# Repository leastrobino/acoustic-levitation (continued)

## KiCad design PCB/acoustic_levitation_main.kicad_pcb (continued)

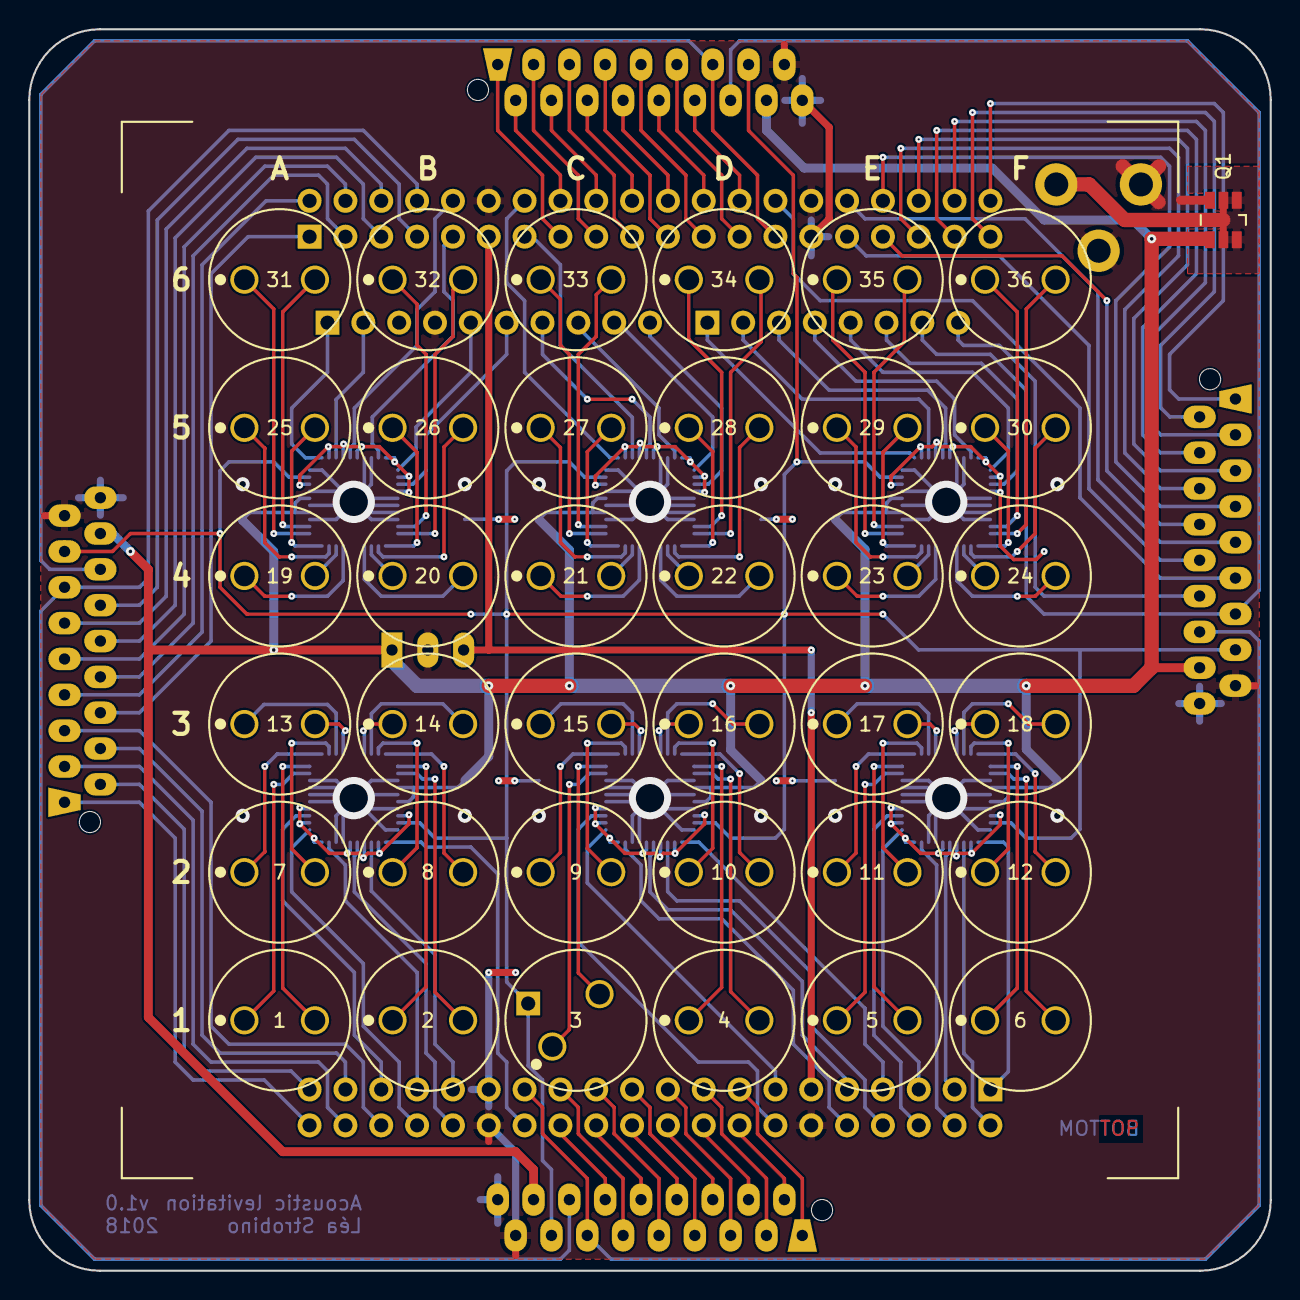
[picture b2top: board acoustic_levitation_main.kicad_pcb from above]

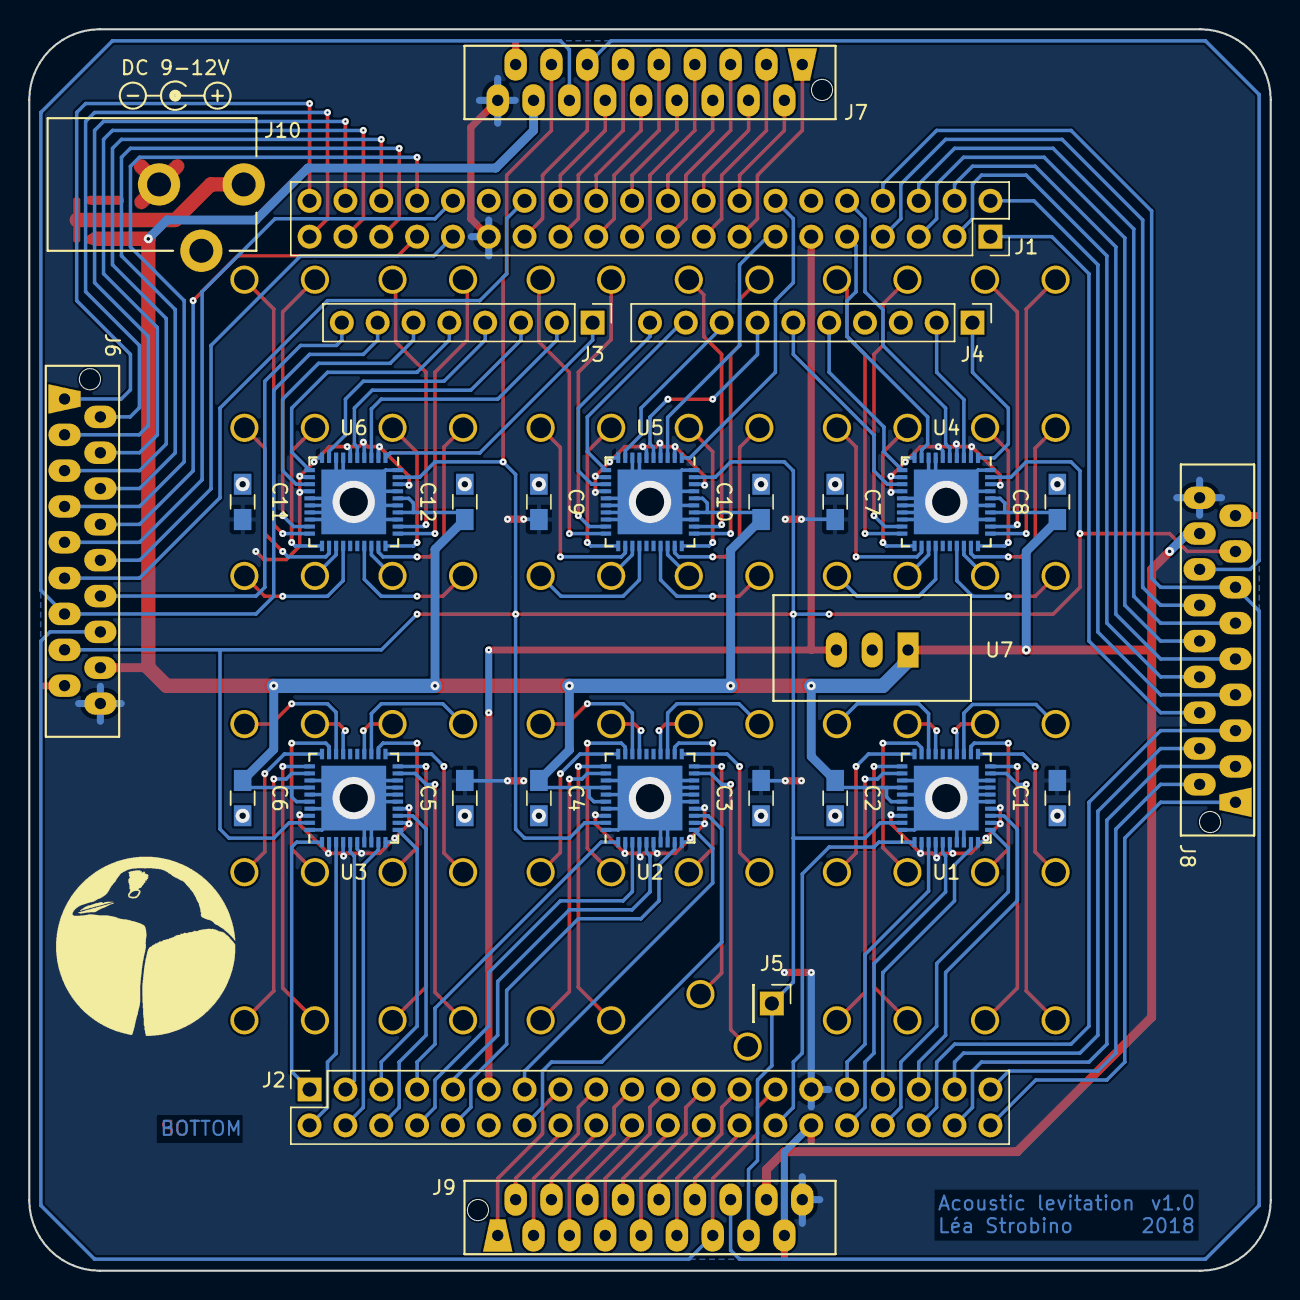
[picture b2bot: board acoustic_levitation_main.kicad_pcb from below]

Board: 2 copper layers, 88.0 x 88.0 mm, 66 parts (29 on the bottom side), 166 nets.

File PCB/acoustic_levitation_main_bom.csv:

% Source: /Users/Lea/Documents/Acoustic levitation/PCB/acoustic_levitation_main.sch
"% Date: Saturday, 03 November 2018 at 16:48:32"
% Component count: 66
Reference,Quantity,Value,Footprint,Manufacturer,Manufacturer part number,Supplier 1,Supplier part number 1,Supplier 2,Supplier part number 2
"C1, C2, C3, C4, C5, C6, C7, C8, C9, C10, C11, C12",12,100n,C_0805_HandSoldering,Wurth Electronics Inc.,885012207072,Digi-Key,732-8061-1-ND,,
J1,1,DE0-Nano-SoC: GPIO 0,Socket_Strip_Straight_2x20_Pitch2.54mm,Samtec Inc.,SSW-120-03-G-D,Digi-Key,SAM11959-ND,,
J2,1,DE0-Nano-SoC: GPIO 1,Socket_Strip_Straight_2x20_Pitch2.54mm,Samtec Inc.,SSW-120-03-G-D,Digi-Key,SAM11959-ND,,
J3,1,DE0-Nano-SoC: JP3,Pin_Header_Straight_1x08_Pitch2.54mm,Wurth Electronics Inc.,61300811121,Digi-Key,732-5321-ND,Distrelec,300-93-649
J4,1,DE0-Nano-SoC: JP2,Pin_Header_Straight_1x10_Pitch2.54mm,Wurth Electronics Inc.,61301011121,Digi-Key,732-2670-ND,Distrelec,300-93-651
J5,1,DE0-Nano-SoC: JP5[3],Pin_Header_Straight_1x01_Pitch2.54mm,Wurth Electronics Inc.,61300111121,Digi-Key,732-5314-ND,Distrelec,300-93-642
"J6, J7, J8, J9",4,8-215079-8,TE_8-215079-8,TE Connectivity AMP Connectors,8-215079-8,Digi-Key,A99466CT-ND,,
J10,1,PJ-102AH,CUI_PJ-102AH,CUI Inc.,PJ-102AH,Digi-Key,CP-102AH-ND,,
Q1,1,Si3421DV,TSOP-6_2.9x1.5mm_Pitch0.95mm,Vishay Siliconix,SI3421DV-T1-GE3,Digi-Key,SI3421DV-T1-GE3CT-ND,,
"TR1, TR2, TR3, TR4, TR5, TR6, TR7, TR8, TR9, TR10, TR11, TR12, TR13, TR14, TR15, TR16, TR17, TR18, TR19, TR20, TR21, TR22, TR23, TR24, TR25, TR26, TR27, TR28, TR29, TR30, TR31, TR32, TR33, TR34, TR35, TR36",36,MA40S4S,Murata_MA40S4S_TE_8134-HC-8P2,Murata,MA40S4S,Digi-Key,490-7707-ND,,
"U1, U2, U3, U4, U5, U6",6,MAX17079,QFN-40-1EP_6x6mm_Pitch0.5mm_HandSoldering,Maxim Integrated,MAX17079GTL+,Digi-Key,MAX17079GTL+-ND,,
U7,1,TSR2-2450,Traco_TSR2,Traco Power,TSR 2-2450,Mouser,495-TSR2-2450,Distrelec,300-67-301

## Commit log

2018-06-03 Added PCB
2018-06-03 Added video demonstrations
2018-06-03 Added documentation
2018-06-03 Added VHDL
2018-06-05 Added BOM
2018-06-10 Added C
2018-06-10 Added pictures
2018-06-10 Updated documentation
2018-06-13 Added phase resolution
2018-06-15 Added Linux scripts
2018-06-15 Added LED & buttons assignments
2018-11-04 Upgraded PCB to KiCad 5
2018-11-17 Code formatting & optimization
    Reduced FPGA logic elements utilization
2018-11-17 Added VHDL simulations
2018-11-25 Added CAD export
2019-01-02 Added license
